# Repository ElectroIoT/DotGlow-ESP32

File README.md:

<p align="center">
  <b>A WiFi + Bluetooth LED matrix clock for ESP32 and ESP32-S3, with its own Android app.</b><br>
  Set it up from your phone in two minutes: no computer, no app accounts, no cloud.
</p>

---

▶ **Watch the 30-second demo:** [YouTube Short](https://www.youtube.com/watch?v=RAMwpgyiXoM)

## Get the app (closed testing)

The DotGlow Android app is in **closed testing on Google Play**. Anyone in the tester group gets it:

1. Join the Google Group **[devmeettesters@googlegroups.com](https://groups.google.com/g/devmeettesters)**
   with the Google account you use on Play.
2. Open **[play.google.com/apps/testing/com.electroiot.dotglow](https://play.google.com/apps/testing/com.electroiot.dotglow)**
   and tap **Become a tester**.
3. Install the app from Google Play and keep it installed for at least 14 days.

Details: [mtpcode.com/apps/dotglow.html](https://mtpcode.com/apps/dotglow.html) · feedback: admin@mtpcode.com

## Contents

[Repository map](#repository-map) · [Features](#features) · [How it works](#how-it-works) · [Parts](#parts) · [Wiring](#wiring) ·
[Install the firmware](#install-the-firmware) · [First setup](#first-setup) · [Using the clock](#using-the-clock) ·
[Stopwatch](#stopwatch) · [Updates](#updates) · [Troubleshooting](#troubleshooting) · [For developers](#for-developers) ·
[Roadmap](#roadmap) · [Credits](#credits)

## Repository map

| Folder | What is in it |
|---|---|
| [`src/`](src) | the firmware (C++, PlatformIO): display, clock, WiFi, web dashboard, Bluetooth |
| [`platformio.ini`](platformio.ini) | build settings for ESP32, ESP32-S3 and test builds |
| [`desktop-flasher/`](desktop-flasher) | a small Windows tool to flash a board over USB |
| [`tools/`](tools) · [`release/`](release) | scripts that build the release images and the firmware list the app reads |
| [`hardware/pcb/`](hardware/pcb/README.md) | the custom DotGlow V1 circuit board (schematic, Gerbers, [BOM](hardware/pcb/bom/README.md), 3D renders) |
| [`hardware/enclosure/`](hardware/enclosure) | 3D-printable cases (STL + OpenSCAD) |
| [`docs/`](docs/README.md) | architecture, Bluetooth protocol, development and release guides, pictures |

Related repo: the Android app, [DotGlow-Android](https://github.com/ElectroIoT/DotGlow-Android).

## Features

| | |
|---|---|
| 📱 **Android app over Bluetooth** | Every setting, WiFi setup, firmware updates, live previews ([DotGlow-Android](https://github.com/ElectroIoT/DotGlow-Android)) |
| 🔒 **Secure pairing** | 6-digit PIN shown on the LED display, encrypted Bluetooth (LE Secure Connections) |
| 🌐 **Web dashboard too** | Settings page on the clock's IP address, with a login |
| 🕒 **Internet time** | NTP with time zones and daylight saving, 12 / 24 hour, leading zero, blinking colon, seconds bar, date |
| ✨ **Animations** | 6 digit-change styles, 5 effects (hourly and at power-on), scrolling messages, special days (birthdays...) |
| 🌙 **Brightness** | Manual, night mode with its own brightness (or display off), optional light sensor (LDR) |
| ⏱️ **Stopwatch** | From the app or with an optional push button |
| 🔄 **Rotate 180°** | Mounted upside down? One tap in the app, or double-press BOOT |
| 🧱 **4 to 16 modules** | 8x32 up to 8x128, any module type (FC-16, generic, Parola, IC-Station), mirror / flip |
| ⬆️ **Updates** | From GitHub over WiFi, from the app over Bluetooth, or a new board straight from the phone over USB |
| 🛟 **Safe mode** | After repeated crashes it starts with only WiFi + updates, so a bad update can always be fixed |

### Digit-change styles

| Roll down | Roll up | Dissolve |
|:-:|:-:|:-:|
|  |  |  |
| **Slide** | **Flip** | **Drop & bounce** |
|  |  |  |

### Effects (every hour, at power-on, or on demand)

| Sparkle | Wipe | Rain |
|:-:|:-:|:-:|
|  |  |  |
| **Boxes** | **Pac-Man** | **Stopwatch** |
|  |  |  |

All pictures are generated from the firmware's own fonts and frame logic (`tools/make_images.py`), so they match the real display.

## How it works

- The **app** talks to the clock over **Bluetooth LE**: paired once with the PIN on the display, then encrypted.
- The **clock** gets the time over **WiFi** and checks for updates. It works on its own; the phone is only for setup and control.
- The same settings are on the clock's **web page** (any browser on the same WiFi).
- Protocol details: [docs/PROTOCOL.md](docs/PROTOCOL.md).

## Parts

| Part | Notes |
|---|---|
| ESP32-S3 DevKitC-1 **or** ESP32 DevKit (WROOM-32) | Any flash size from 4 MB. ESP32-S2 has no Bluetooth: not supported |
| MAX7219 4-in-1 LED matrix (8x32) | The common blue "FC-16" boards. Chain more for 8x64 ... 8x128 |
| 5 jumper wires | Female-female for most boards |
| **5 V / 1 A (or stronger) phone charger** + cable | **Required.** A computer USB port is too weak for the display, see [power](#power-read-this) |
| 470-1000 µF capacitor | Across VCC / GND at the display (+ leg to VCC). Strongly recommended |
| *Optional:* LDR + 10 kΩ resistor | Automatic brightness |
| *Optional:* push button | [Stopwatch](#stopwatch) without the phone |
| *Optional:* 3D-printed case | [hardware/enclosure](hardware/enclosure): leaning desk case, smoked acrylic front, DC jack; STLs for ESP32-S3, ESP32 DevKit, NodeMCU, D1 mini |

<p align="center"></p>

Using an ESP8266 / NodeMCU instead? That is the [ESP8266 Matrix Clock](https://github.com/ElectroIoT/ESP8266-Matrix-Clock) (WiFi + web page, no Bluetooth). The DotGlow app can install it too.

## Wiring

| ESP32-S3 DevKitC-1 | ESP32 DevKit |
|:-:|:-:|
|  |  |

| MAX7219 | ESP32-S3 | ESP32 DevKit |
|---|---|---|
| VCC | 5V | VIN (5V) |
| GND | GND | GND |
| DIN | GPIO11 | GPIO23 |
| CS | GPIO10 | GPIO5 |
| CLK | GPIO12 | GPIO18 |
| *LDR (optional)* | GPIO1 | GPIO34 |
| *Stopwatch button (optional)* | GPIO4 | GPIO13 |

**Light sensor:** LDR from 3V3 to the LDR pin, 10 kΩ from that pin to GND, then turn on *Auto brightness*.

> ⚠️ **ESP32 DevKit:** never use the pins labelled **CLK, SD0, SD1, SD2, SD3, CMD**. They are the board's flash
> memory pins; a wire there stops the board from starting (`invalid header: 0xffffffff`). The display's CLK goes to
> **D18**, not to the pin called "CLK". Always wire the display's **IN** end (pins marked DIN), not DOUT.

### Power (read this)

Power the clock from a **5 V / 1 A (or stronger) phone charger**. A computer's USB port cannot drive the display:
the LEDs stay dim, all LEDs stay on or show garbage, the board keeps restarting and drops off USB.
That was the cause of every "display does not work" case during testing; a 1 A charger fixed all of them.
Flashing from a computer is fine; test the display on the charger.

### More modules and power

Connect **OUT** of one board to **IN** of the next, then set the module count in the app (*Display*).

| Modules | Display | Supply |
|---|---|---|
| 4 | 8x32 | 5 V / 1 A (USB is fine) |
| 8 | 8x64 | 5 V / 2 A, separate supply |
| 12 | 8x96 | 5 V / 3 A |
| 16 | 8x128 | 5 V / 4 A |

Above 4 modules feed 5 V to the boards directly (not through the ESP32), with a 470-1000 µF capacitor at each board.

## Install the firmware

### A. From your phone (easiest)

1. Install the **DotGlow** app (closed testing: see [Get the app](#get-the-app-closed-testing)).
2. Plug the board into the phone with a USB-OTG adapter (or a USB-C data cable).
3. In the app: **Install firmware → Find my board → Install**. The app detects ESP32 / ESP32-S3 and writes the right image (about 20-60 s).

### A1. From your browser (nothing to install)

Open **[mtpcode.com/flash](https://mtpcode.com/flash/)** in Chrome or Edge on a computer, plug the board in, press
**Install**. ESP32, ESP32-S3 and ESP8266 (NodeMCU / D1 mini).

### A2. From a PC (no phone, no PlatformIO)

[desktop-flasher](desktop-flasher): a small program that finds the board, downloads the latest firmware and installs it
(window or command line, Windows / Linux / macOS). `python desktop-flasher/dotglow_flasher.py` or the `.exe`.

### B. PlatformIO

```bash
pio run -e esp32s3 -t upload --upload-port COM5     # ESP32-S3 (the "USB" port)
pio run -e esp32dev -t upload                        # classic ESP32
```

### C. esptool, with a release image

```bash
esptool.py write_flash 0x0 dotglow-esp32s3-full.bin
```

Full images (bootloader + partitions + app) are made by `python tools/release.py`.

## First setup

1. **Power on.** The clock plays its welcome animation and shows *manoranjan.dev*.
2. **Pair.** In the app tap **DotGlow-XXXX**. The clock shows a 6-digit PIN; type it in Android's pairing request.
3. **WiFi.** Tap **Set up**, pick your network, type the password. The clock restarts and fetches the time.
4. **Done.** Change anything from the app. The clock scrolls its IP address for the web page.

No app? The clock opens a WiFi hotspot **DotGlow-XXXX**; join it and the setup page opens (or http://192.168.4.1).

## Using the clock

- **App:** brightness, night mode, time format and zone, digit style, effects, messages, special days, display layout, updates, security.
- **Web page:** `http://<clock IP>` or `http://dotglow.local`, with an optional login password.
- **BOOT button:** short press = scroll the IP · **double press = rotate the display 180°** · hold 5 s = WiFi setup ·
  hold 10 s = remove the web password.

## Stopwatch

**On the display**

| Running | Paused (blinks) | After an hour |
|:-:|:-:|:-:|
|  |  |  |
| `MM:SS`, tenths fill the bottom row | Digits blink, time kept | `HH:MM`, the bottom row fills once a minute |

**Button wiring (optional)**

- **In the app:** *Stopwatch* → Start / Pause / Reset / Back to the clock. The app shows a live copy of the display.
- **With a button** (optional, from GPIO4 on the S3 / GPIO13 on the ESP32 to GND, no resistor needed):
  tap = start / pause (from the clock: open the stopwatch), hold = reset, hold at 0 = back to the clock.
- With 6 or more modules it shows `HH:MM:SS` all the time.

## Updates

| How | When to use |
|---|---|
| **GitHub over WiFi** | Automatic at night (if enabled) or *Updates → Check now* |
| **App over Bluetooth** | *Updates → Update over Bluetooth*: no WiFi needed, about 30 s |
| **USB from the phone** | New or broken boards: *Install firmware* |
| **Web upload** | *Upload firmware.bin* on the web page (password protected) |

## Hardware: the DotGlow V1 board

<p align="center"></p>

A custom 128 x 31.1 mm PCB that stacks on the back of the 4-in-1 MAX7219 module: ESP32-S3, USB-C, I2S speaker amplifier,
stopwatch / LDR / DHT22 connectors, and an I2C port for a clock chip. Schematic, Gerbers, BOM, 3D renders and the
KiCad / EasyEDA files are in [`hardware/pcb/`](hardware/pcb/README.md). Untested V1. ▶ [Watch the PCB Short](https://www.youtube.com/shorts/DH94otuCLPg).

## Troubleshooting

| Problem | Fix |
|---|---|
| Board light is on but the app doesn't see the clock | **Join the grounds:** display GND, board GND and the power supply GND must be connected together. Use a stable 5 V supply: a weak one restarts the board when Bluetooth starts |
| Dim, all LEDs stuck on, or garbage | **Power:** use a 5 V / 1 A charger, not a computer USB port; add the capacitor |
| Only the first module works | A broken link between modules (re-solder the joints between module 1 and 2) |
| ESP32 doesn't start after wiring | A wire is on CMD / SD0-SD3 / CLK (flash pins): move it |
| Text scrambled / mirrored | App → Display → module type / mirror / flip |
| Upside down | App → Display → **Rotate 180°**, the rotate button on the dashboard, or **double-press BOOT** |
| Keeps restarting | Better 5 V supply, add the capacitor; after 3 crashes it starts in safe mode |
| Can't pair | Use the PIN on the display (not 0000 / 1234). After a factory reset the app re-pairs by itself |
| "Getting time..." forever | WiFi has no internet, or the time zone is wrong (App → Clock & time) |
| Board drops off USB / flash stops half way | Take the display's 5 V wire off the board while flashing (the display draws more than USB gives); short thick data cable, another port |
| USB install fails | Use a data cable; hold BOOT, tap RESET, release BOOT, try again |

## For developers

| Doc | What's in it |
|---|---|
| [docs/ARCHITECTURE.md](docs/ARCHITECTURE.md) | Modules, main loop, settings storage, safe mode, OTA |
| [docs/PROTOCOL.md](docs/PROTOCOL.md) | Bluetooth GATT service, request / response format, every operation |
| [docs/DEVELOPMENT.md](docs/DEVELOPMENT.md) | Build envs, test build, serial gotchas, testing with the app |
| [docs/RELEASE.md](docs/RELEASE.md) | Version bump, release images, publishing the firmware catalog |
| [CHANGELOG.md](CHANGELOG.md) | What changed in each version |
| [CLAUDE.md](CLAUDE.md) | Quick brief for AI coding assistants |

## Roadmap

| Phase | What | Status |
|---|---|---|
| 1 | ESP32 / ESP32-S3 port of the ESP8266 Matrix Clock | ✅ working on an ESP32-S3 with the real MAX7219 display |
| 2 | Bluetooth service + protocol | ✅ tested on a Motorola Edge 40 Neo (Android 15) |
| 3 | Android app: pairing, dashboard | ✅ |
| 4 | Android app: all settings, WiFi setup, app PIN lock, setup guide | ✅ |
| 5 | Firmware updates over Bluetooth | ✅ 1.2 MB in 26 s |
| 6 | Flash a new board from the phone over USB-OTG (ESP32, ESP32-S3, ESP8266) | ✅ tested on an ESP32-S3 |
| 6b | Stopwatch with an optional button | ✅ |
| 6c | 3D-printed case (OpenSCAD, parametric) | 🟡 designed, test print pending |
| 6d | Temperature + humidity from a DHT22 (shown on the display and in the app); the case has a pocket for it | ⬜ planned |
| 7 | Public release | ⬜ |

## Credits

- Based on the author's own [ESP8266 Matrix Clock](https://github.com/ElectroIoT/ESP8266-Matrix-Clock) (MIT).
- [MD_MAX72XX](https://github.com/MajicDesigns/MD_MAX72XX) by Marco Colli (LGPL-2.1) for the display driver.
- [NimBLE-Arduino](https://github.com/h2zero/NimBLE-Arduino) (Apache-2.0) for Bluetooth.
- [ArduinoJson](https://arduinojson.org) by Benoît Blanchon (MIT).
- [Arduino-ESP32 core](https://github.com/espressif/arduino-esp32) (LGPL-2.1).

## License

MIT, see [LICENSE](LICENSE). Made with care in India by [Manoranjan](https://manoranjan.dev) · [ElectroIoT](https://electroiot.in).

### Name and logo

The code is MIT licensed, but the **DotGlow** name, logo and app icon are not covered by the licence.
Forks and rebuilt apps are welcome; please publish them under your own name, icon and package
(not `com.electroiot.dotglow`), so users can tell them apart from the official app.

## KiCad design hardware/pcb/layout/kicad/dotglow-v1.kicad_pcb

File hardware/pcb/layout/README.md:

# DotGlow V1 layout only (no routing)

For building your own board in EasyEDA with your own parts. No copper tracks, just the outline and part positions.

| File | Use |
|---|---|
| `dotglow-v1-layout.png` / `.pdf` | picture of the outline, holes, keep-out and part positions |
| `dotglow-v1-outline-holes.dxf` | **start here**: board outline 128 x 33, four 3.2 mm mounting holes, antenna keep-out, display header pins, USB-C (separate layers, mm, origin bottom-left, Y up) |
| `dotglow-v1-full-layout.dxf` | everything in one file: outline, part courtyards, silkscreen, drawings (mm, origin bottom-left) |
| `dotglow-v1-placement.csv` | every part: ref, value, footprint, part, **X / Y in mm from the top-left corner (X right, Y down)**, rotation |
| `kicad/` | the same placement as a KiCad project (placed, not routed) |

## Board

- 128 x 33 mm, two layers, origin at the top-left corner.
- **ESP32 antenna keep-out: X < 6.9 mm, full height.** No copper, no parts, no pour there. The ESP32-S3-WROOM-1 (25.5 x 18 mm) sits at the left edge, antenna end to the left.
- Mounting holes `H1..H4` (3.2 mm for M3) are **placeholders**: (23.5, 3), (21, 30), (125, 3), (125, 30). Move them to match your matrix module.
- `J2` (5-pin DISPLAY IN header, VCC GND DIN CS CLK) is at (125.5, 11.42), vertical (pin 1 at the top, 2.54 mm pitch). Move it to match your matrix module.
- USB-C `J1` (108, 29) sits on the bottom edge. The speaker JST `J5` and the solder pads `TP1` / `TP2` are next to the buttons.

## EasyEDA import

- File > Import > DXF, pick `dotglow-v1-outline-holes.dxf` (units: mm).
- Or File > Import > KiCad, `kicad/dotglow-v1.kicad_pcb`, and swap the footprints for your own parts. Keep the positions from the CSV.
- Net names and pin assignments are in `../README.md` (GPIO table) and `kicad/dotglow-v1.kicad_sch`.

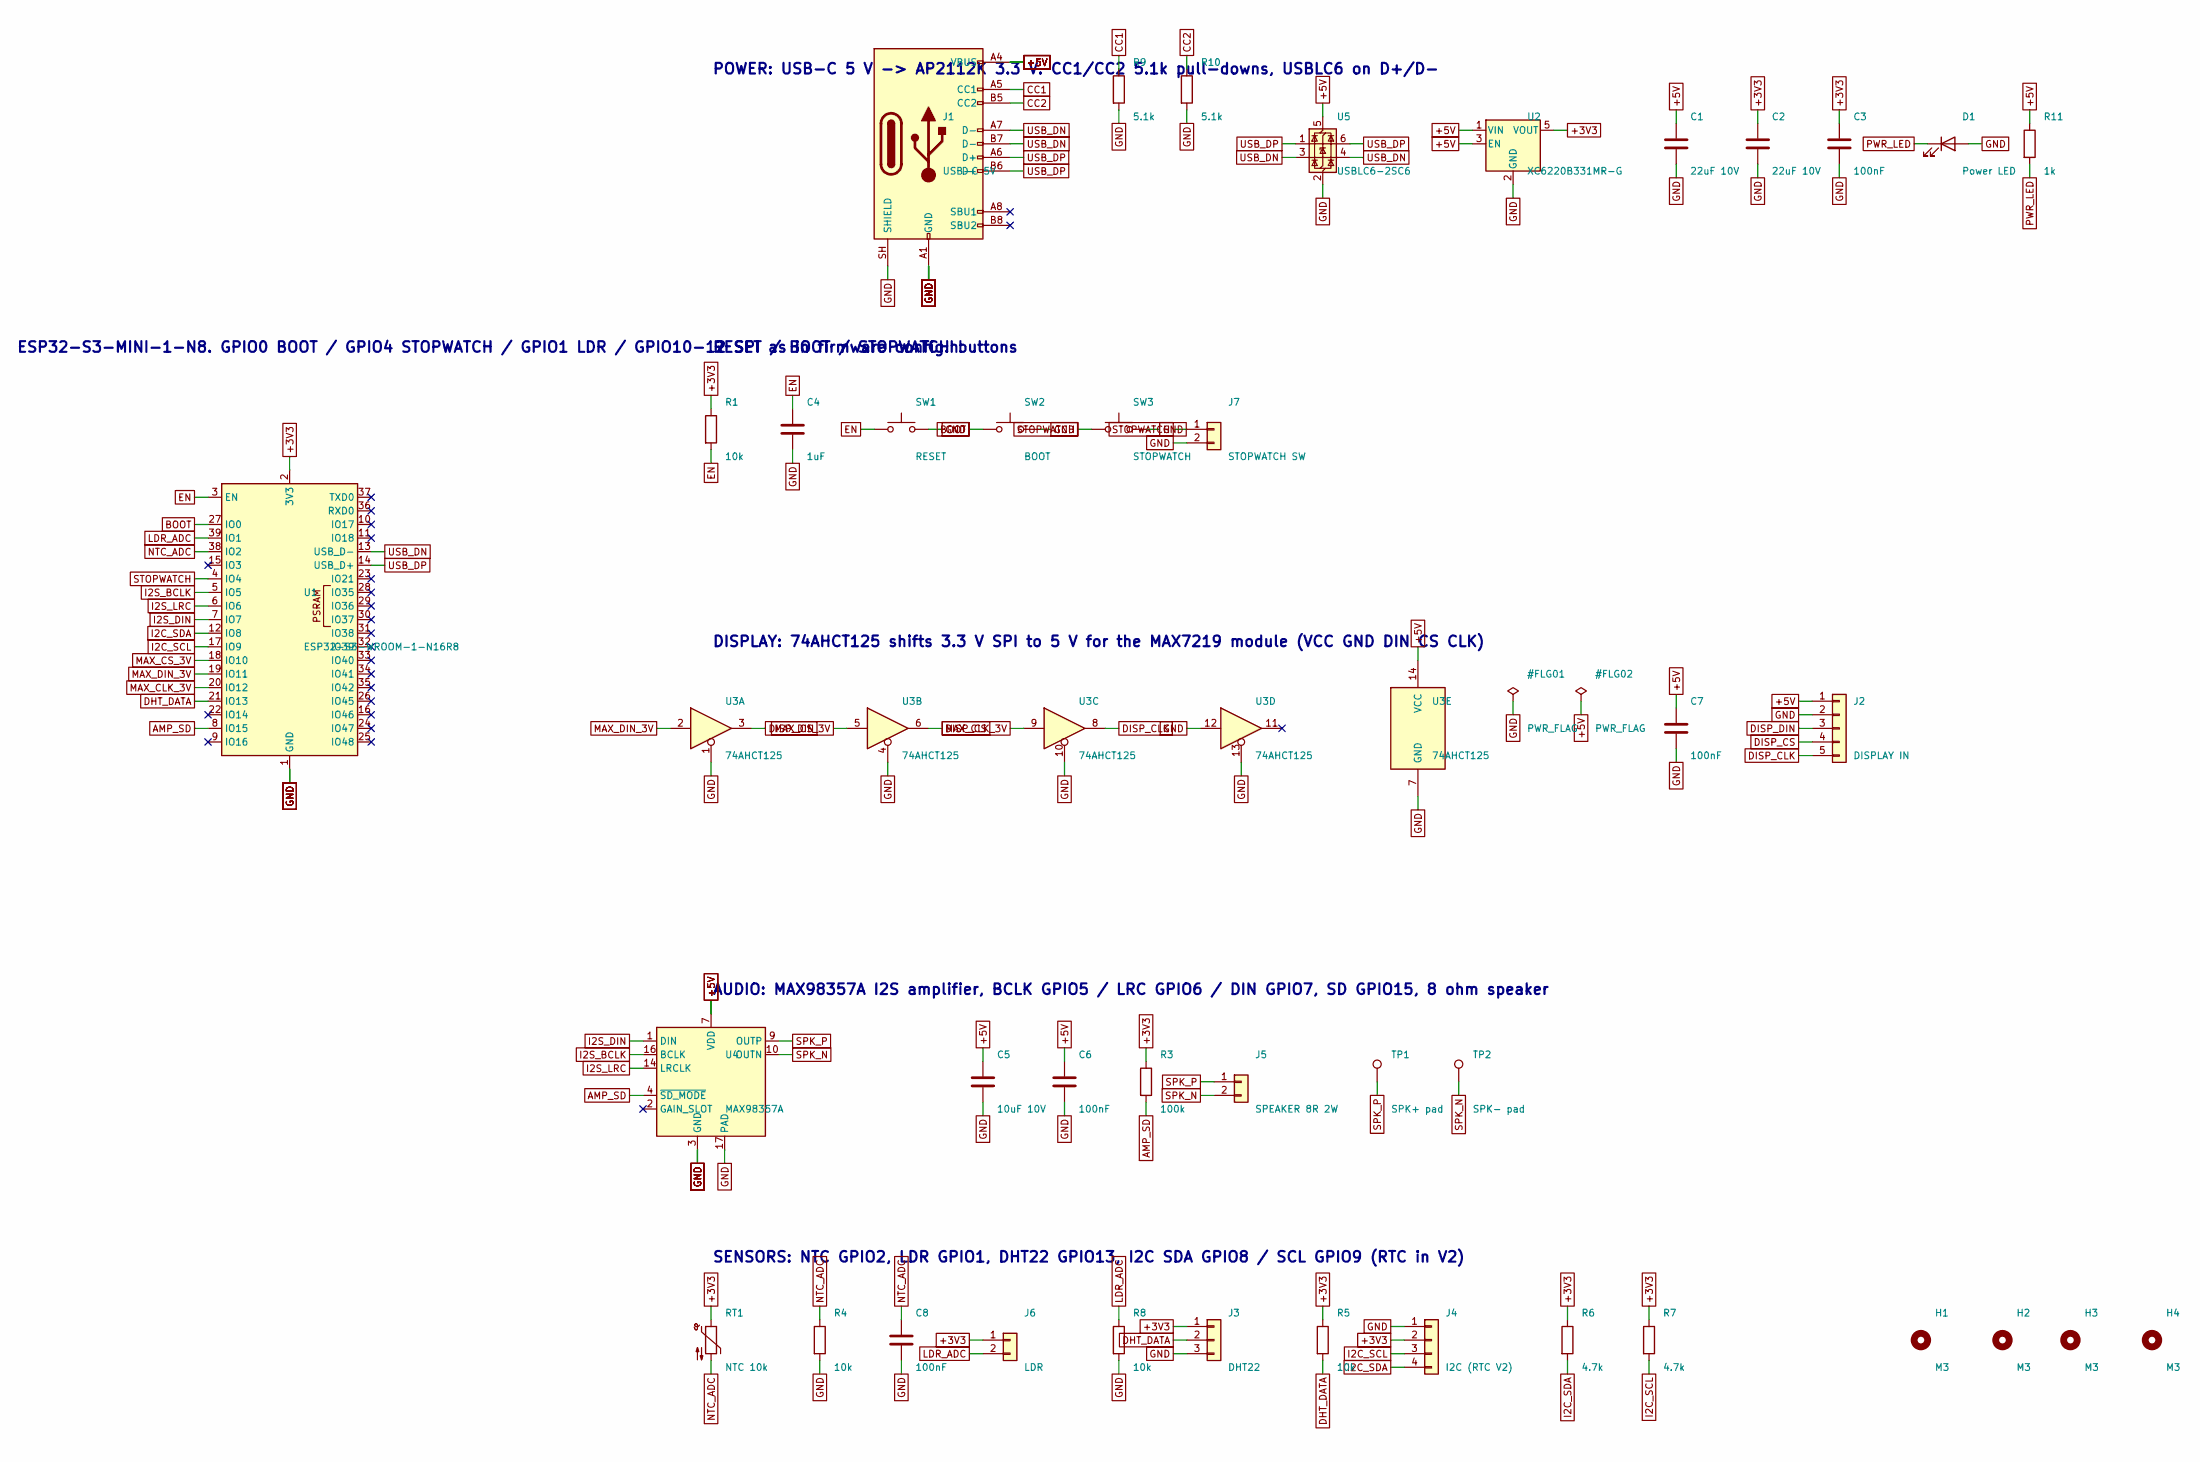
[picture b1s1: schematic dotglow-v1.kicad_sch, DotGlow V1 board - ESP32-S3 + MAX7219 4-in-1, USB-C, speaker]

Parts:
C1, C2: 22uF 10V; C_1206_3216Metric
C3, C6, C7, C8: 100nF; C_0805_2012Metric
C4: 1uF; C_0805_2012Metric
C5: 10uF 10V; C_0805_2012Metric
D1: Power LED; LED_0805_2012Metric
H1, H2, H3, H4: M3; MountingHole_3.2mm_M3
J1: USB-C 5V; USB_C_Receptacle_GCT_USB4105-xx-A_16P_TopMnt_Horizontal
J2: DISPLAY IN; PinHeader_1x05_P2.54mm_Vertical
J3: DHT22; JST_XA_B03B-XASK-1_1x03_P2.50mm_Vertical
J4: I2C (RTC V2); JST_XA_B04B-XASK-1-A_1x04_P2.50mm_Vertical
J5: SPEAKER 8R 2W; JST_XA_B02B-XASK-1-A_1x02_P2.50mm_Vertical
J6: LDR; JST_XA_B02B-XASK-1-A_1x02_P2.50mm_Vertical
J7: STOPWATCH SW; JST_XA_B02B-XASK-1-A_1x02_P2.50mm_Vertical
R1, R4, R5, R8: 10k; R_0805_2012Metric
R3: 100k; R_0805_2012Metric
R6, R7: 4.7k; R_0805_2012Metric
R9, R10: 5.1k; R_0805_2012Metric
R11: 1k; R_0805_2012Metric
RT1: NTC 10k; R_0603_1608Metric
SW1: RESET; SW_SPST_B3S-1000
SW2: BOOT; SW_SPST_B3S-1000
SW3: STOPWATCH; SW_SPST_B3S-1000
TP1: SPK+ pad; TestPoint_Pad_D2.5mm
TP2: SPK- pad; TestPoint_Pad_D2.5mm
U1: ESP32-S3-WROOM-1-N16R8; ESP32-S3-WROOM-1
U2: XC6220B331MR-G; SOT-23-5
U3: 74AHCT125; SOIC-14_3.9x8.7mm_P1.27mm
U4: MAX98357A; TQFN-16-1EP_3x3mm_P0.5mm_EP1.6x1.6mm
U5: USBLC6-2SC6; SOT-23-6

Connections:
+3V3: C2.1, C3.1, J3.1, J4.2, J6.1, R1.1, R3.1, R5.1, R6.1, R7.1, RT1.1, U1.2 (3V3), U2.5 (VOUT)
+5V: C1.1, C5.1, C6.1, C7.1, J1.A4 (VBUS), J1.A9 (VBUS), J1.B4 (VBUS), J1.B9 (VBUS), J2.1, R11.1, U2.1 (VIN), U2.3 (EN), U3.14 (VCC), U4.7 (VDD), U4.8 (VDD), U5.5 (VBUS)
AMP_SD: R3.2, U1.8 (IO15), U4.4 (~SD_MODE)
BOOT: SW2.1, U1.27 (IO0)
CC1: J1.A5 (CC1), R9.1
CC2: J1.B5 (CC2), R10.1
DHT_DATA: J3.2, R5.2, U1.21 (IO13)
DISP_CLK: J2.5, U3.8
DISP_CS: J2.4, U3.6
DISP_DIN: J2.3, U3.3
EN: C4.1, R1.2, SW1.1, U1.3 (EN)
GND: C1.2, C2.2, C3.2, C4.2, C5.2, C6.2, C7.2, C8.2, D1.2 (A), J1.A1 (GND), J1.A12 (GND), J1.B1 (GND), J1.B12 (GND), J1.SH (SHIELD), J2.2, J3.3, J4.1, J7.2, R4.2, R8.2, R9.2, R10.2, SW1.2, SW2.2, SW3.2, U1.1 (GND), U1.40 (GND), U1.41 (GND), U2.2 (GND), U3.1, U3.4, U3.7 (GND), U3.10, U3.12, U3.13, U4.3 (GND), U4.11 (GND), U4.15 (GND), U4.17 (PAD), U5.2 (GND)
I2C_SCL: J4.3, R7.2, U1.17 (IO9)
I2C_SDA: J4.4, R6.2, U1.12 (IO8)
I2S_BCLK: U1.5 (IO5), U4.16 (BCLK)
I2S_DIN: U1.7 (IO7), U4.1 (DIN)
I2S_LRC: U1.6 (IO6), U4.14 (LRCLK)
LDR_ADC: J6.2, R8.1, U1.39 (IO1)
MAX_CLK_3V: U1.20 (IO12), U3.9
MAX_CS_3V: U1.18 (IO10), U3.5
MAX_DIN_3V: U1.19 (IO11), U3.2
NTC_ADC: C8.1, R4.1, RT1.2, U1.38 (IO2)
PWR_LED: D1.1 (K), R11.2
SPK_N: J5.2, TP2.1, U4.10 (OUTN)
SPK_P: J5.1, TP1.1, U4.9 (OUTP)
STOPWATCH: J7.1, SW3.1, U1.4 (IO4)
USB_DN: J1.A7 (D-), J1.B7 (D-), U1.13 (USB_D-), U5.3 (I/O2), U5.4 (I/O2)
USB_DP: J1.A6 (D+), J1.B6 (D+), U1.14 (USB_D+), U5.1 (I/O1), U5.6 (I/O1)

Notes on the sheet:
POWER: USB-C 5 V -> AP2112K 3.3 V. CC1/CC2 5.1k pull-downs, USBLC6 on D+/D-
ESP32-S3-MINI-1-N8. GPIO0 BOOT / GPIO4 STOPWATCH / GPIO1 LDR / GPIO10-12 SPI as in firmware config.h
RESET / BOOT / STOPWATCH buttons
DISPLAY: 74AHCT125 shifts 3.3 V SPI to 5 V for the MAX7219 module (VCC GND DIN CS CLK)
AUDIO: MAX98357A I2S amplifier, BCLK GPIO5 / LRC GPIO6 / DIN GPIO7, SD GPIO15, 8 ohm speaker
SENSORS: NTC GPIO2, LDR GPIO1, DHT22 GPIO13, I2C SDA GPIO8 / SCL GPIO9 (RTC in V2)

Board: 2 copper layers, 41 parts (0 on the bottom side), 28 nets, no tracks yet.

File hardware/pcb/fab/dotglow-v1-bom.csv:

Comment,Designator,Footprint,Qty,Suggested part / note
22uF 10V,"C1,C2",C_1206_3216Metric,2,
100nF,"C3,C6,C7,C8",C_0805_2012Metric,4,
1uF,C4,C_0805_2012Metric,1,
10uF 10V,C5,C_0805_2012Metric,1,
Power LED,D1,LED_0805_2012Metric,1,
USB-C 5V,J1,USB_C_Receptacle_GCT_USB4105-xx-A_16P_TopMnt_Horizontal,1,GCT USB4105-GF-A
DISPLAY IN,J2,PinHeader_1x05_P2.54mm_Vertical,1,XFCN PZ254V-11-05P 1x5 pin header (LCSC C492404)
DHT22,J3,JST_XA_B03B-XASK-1_1x03_P2.50mm_Vertical,1,JST B03B-XASK-1 (LCSC C265055)
I2C (RTC V2),J4,JST_XA_B04B-XASK-1-A_1x04_P2.50mm_Vertical,1,JST B04B-XASK-1-A (LCSC C491709)
SPEAKER 8R 2W,J5,JST_XA_B02B-XASK-1-A_1x02_P2.50mm_Vertical,1,JST B02B-XASK-1-A (LCSC C265077)
LDR,J6,JST_XA_B02B-XASK-1-A_1x02_P2.50mm_Vertical,1,JST B02B-XASK-1-A (LCSC C265077)
STOPWATCH SW,J7,JST_XA_B02B-XASK-1-A_1x02_P2.50mm_Vertical,1,JST B02B-XASK-1-A (LCSC C265077)
10k,"R1,R4,R5,R8",R_0805_2012Metric,4,
1k,R11,R_0805_2012Metric,1,
100k,R3,R_0805_2012Metric,1,
4.7k,"R6,R7",R_0805_2012Metric,2,
5.1k,"R10,R9",R_0805_2012Metric,2,
NTC 10k,RT1,R_0603_1608Metric,1,"10k NTC, B=3950, 0603 (e.g. NCP18XH103F03RB)"
RESET,SW1,SW_SPST_B3S-1000,1,6x6 SMD tact switch
BOOT,SW2,SW_SPST_B3S-1000,1,6x6 SMD tact switch
STOPWATCH,SW3,SW_SPST_B3S-1000,1,6x6 SMD tact switch
SPK+ pad,TP1,TestPoint_Pad_D2.5mm,1,
SPK- pad,TP2,TestPoint_Pad_D2.5mm,1,
ESP32-S3-WROOM-1-N16R8,U1,ESP32-S3-WROOM-1,1,ESP32-S3-WROOM-1-N16R8 (LCSC C2913202)
XC6220B331MR-G,U2,SOT-23-5,1,"XC6220B331MR-G (LCSC C86534), 1 A, pin-compatible with AP2112K-3.3 (C51118)"
74AHCT125,U3,SOIC-14_3.9x8.7mm_P1.27mm,1,SN74AHCT125DR (LCSC C155176)
MAX98357A,U4,TQFN-16-1EP_3x3mm_P0.5mm_EP1.6x1.6mm,1,MAX98357AETE+T (LCSC C910544)
USBLC6-2SC6,U5,SOT-23-6,1,USBLC6-2SC6

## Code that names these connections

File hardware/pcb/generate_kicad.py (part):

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ESP_NETS = {
    "3V3": "+3V3", "EN": "EN",
    "IO0": "BOOT",            # PIN_BUTTON (hold 5 s = WiFi setup, hold 10 s = pairing PIN reset) + boot-mode strap
    "IO4": "STOPWATCH",       # PIN_STOPWATCH
    "IO1": "LDR_ADC",         # PIN_LDR (optional LDR from 3V3, 10k to GND on the board)
    "IO2": "NTC_ADC",         # 10k NTC thermistor divider (temperature), new
    "IO10": "MAX_CS_3V",      # PIN_CS  (SPI CS  -> 74AHCT125 -> display CS)
    "IO11": "MAX_DIN_3V",     # SPI MOSI -> 74AHCT125 -> display DIN
    "IO12": "MAX_CLK_3V",     # SPI CLK  -> 74AHCT125 -> display CLK
    "IO5": "I2S_BCLK", "IO6": "I2S_LRC", "IO7": "I2S_DIN",   # MAX98357A amplifier (new)
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part("SW3", "Switch:SW_Push", "STOPWATCH", "Button_Switch_SMD:SW_SPST_B3S-1000", {"1": "STOPWATCH", "2": "GND"}, (225, 95), mpn="6x6 SMD tact switch")

part("J7", "Connector_Generic:Conn_01x02", "STOPWATCH SW", "Connector_JST:JST_XA_B02B-XASK-1-A_1x02_P2.50mm_Vertical",
     {"1": "STOPWATCH", "2": "GND"}, (245, 95), mpn="JST B02B-XASK-1-A (LCSC C265077)", note="external stopwatch push button (in parallel with SW3): pin 1 = GPIO4, pin 2 = GND")

# ---- display: 74AHCT125 level shifter (3.3 V GPIO -> 5 V MAX7219) and the 5-pin connector
part("U3", "74xx:74AHCT125", "74AHCT125", "Package_SO:SOIC-14_3.9x8.7mm_P1.27mm",
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     (150, 150), mpn="SN74AHCT125DR (LCSC C155176)", note="MAX7219 needs >= 3.5 V logic-high at 5 V; the 4th gate is parked")
part("C7", "Device:C", "100nF", FP_C, {"1": "+5V", "2": "GND"}, (330, 150))
part("J2", "Connector_Generic:Conn_01x05", "DISPLAY IN", "Connector_PinHeader_2.54mm:PinHeader_1x05_P2.54mm_Vertical",
     {"1": "+5V", "2": "GND", "3": "DISP_DIN", "4": "DISP_CS", "5": "DISP_CLK"}, (360, 150), mpn="XFCN PZ254V-11-05P 1x5 pin header (LCSC C492404)",
     note="to the MAX7219 module IN header: VCC GND DIN CS CLK (check the order on YOUR module)")

# ---- audio: MAX98357A I2S amplifier + 8 ohm speaker
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     mpn="MAX98357AETE+T (LCSC C910544)", note="GAIN_SLOT floating = 9 dB; SD_MODE high (>1.4 V) = on, mixes L+R")
part("C5", "Device:C", "10uF 10V", FP_C, {"1": "+5V", "2": "GND"}, (200, 215))
part("C6", "Device:C", "100nF", FP_C, {"1": "+5V", "2": "GND"}, (215, 215))
part("R3", "Device:R", "100k", FP_R, {"1": "+3V3", "2": "AMP_SD"}, (230, 215), note="amp on by default; GPIO15 can mute it")
part("J5", "Connector_Generic:Conn_01x02", "SPEAKER 8R 2W", "Connector_JST:JST_XA_B02B-XASK-1-A_1x02_P2.50mm_Vertical",
     {"1": "SPK_P", "2": "SPK_N"}, (250, 215), mpn="JST B02B-XASK-1-A (LCSC C265077)",
     note="2030 cavity speaker (20x30 mm, 8 ohm, 2 W); bridge output: neither wire is ground")
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part("R4", "Device:R", "10k", FP_R, {"1": "NTC_ADC", "2": "GND"}, (170, 265))
part("C8", "Device:C", "100nF", FP_C, {"1": "NTC_ADC", "2": "GND"}, (185, 265))
part("J6", "Connector_Generic:Conn_01x02", "LDR", "Connector_JST:JST_XA_B02B-XASK-1-A_1x02_P2.50mm_Vertical",
     {"1": "+3V3", "2": "LDR_ADC"}, (205, 265), mpn="JST B02B-XASK-1-A (LCSC C265077)", note="optional LDR (GL5528) between 3V3 and the pin")
part("R8", "Device:R", "10k", FP_R, {"1": "LDR_ADC", "2": "GND"}, (225, 265))
part("J3", "Connector_Generic:Conn_01x03", "DHT22", "Connector_JST:JST_XA_B03B-XASK-1_1x03_P2.50mm_Vertical",
     {"1": "+3V3", "2": "DHT_DATA", "3": "GND"}, (245, 265), mpn="JST B03B-XASK-1 (LCSC C265055)", note="optional DHT22: VCC DATA GND (check YOUR module)")
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
    notes = [
        (150, 28, "POWER: USB-C 5 V -> AP2112K 3.3 V. CC1/CC2 5.1k pull-downs, USBLC6 on D+/D-"),
        (20, 80, "ESP32-S3-MINI-1-N8. GPIO0 BOOT / GPIO4 STOPWATCH / GPIO1 LDR / GPIO10-12 SPI as in firmware config.h"),
        (150, 80, "RESET / BOOT / STOPWATCH buttons"),
        (150, 135, "DISPLAY: 74AHCT125 shifts 3.3 V SPI to 5 V for the MAX7219 module (VCC GND DIN CS CLK)"),
        (150, 200, "AUDIO: MAX98357A I2S amplifier, BCLK GPIO5 / LRC GPIO6 / DIN GPIO7, SD GPIO15, 8 ohm speaker"),
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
